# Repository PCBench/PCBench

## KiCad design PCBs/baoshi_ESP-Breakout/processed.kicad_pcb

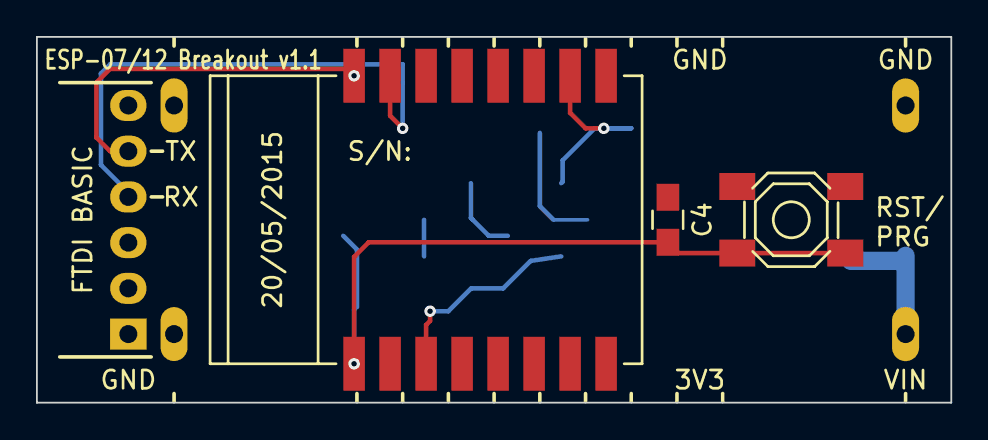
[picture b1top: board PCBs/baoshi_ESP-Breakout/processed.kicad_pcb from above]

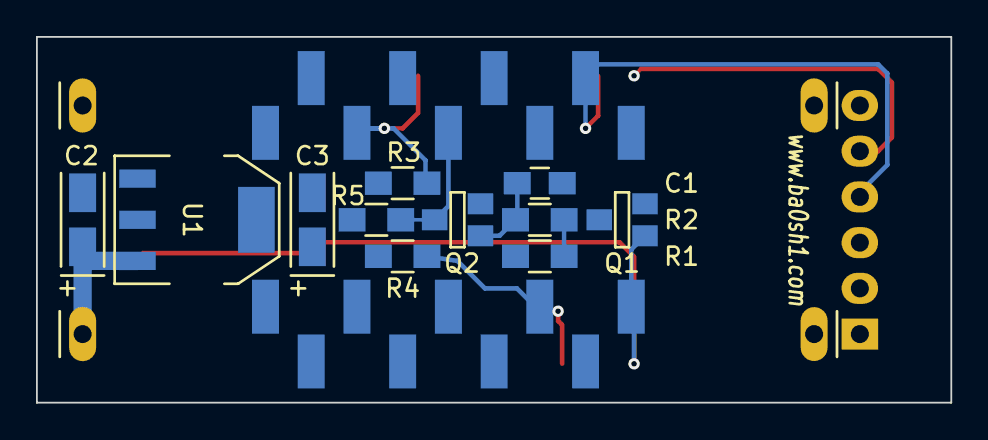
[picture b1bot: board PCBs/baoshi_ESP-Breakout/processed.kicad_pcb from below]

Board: 2 copper layers, 50.8 x 20.3 mm, 17 parts (13 on the bottom side), 9 nets.

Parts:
C1: 2u2; C_0805_HandSoldering
C2: 4u7; TantalC_SizeA_EIA-3216_Wave
C3: 22u; TantalC_SizeA_EIA-3216_Wave
C4: 0.1u; C_0805_HandSoldering
M1: ESP-07
P1: FTDI BASIC; Pin_Header_Angled_1x06
P2: CONN_01X11; SMD-PINHEADER-11A
P3: CONN_01X11; SMD-PINHEADER-11B
Q1, Q2: BSS138; SOT-23-GDS
R1: 470K; R_0805_HandSoldering
R2: 100K; R_0805_HandSoldering
R3, R5: 10K; R_0805_HandSoldering
R4: 47K; R_0805_HandSoldering
SW1: SW_PUSH; PUSH_4x4_SMD
U1: 1117-3.3; SOT-223

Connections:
+5V: P3.11, U1.3
/GPIO0: P2.6, Q2.D, R5.1
/RESET: C4.1, M1.1, P3.2, Q1.G, SW1.2
/RXI: M1.16, P1.5
/TXO: M1.15, P1.4
unnamed: C1.1, Q2.G, R2.1
unnamed: M1.3, R4.1
unnamed: M1.10, R3.2
unnamed: R1.2, R2.2

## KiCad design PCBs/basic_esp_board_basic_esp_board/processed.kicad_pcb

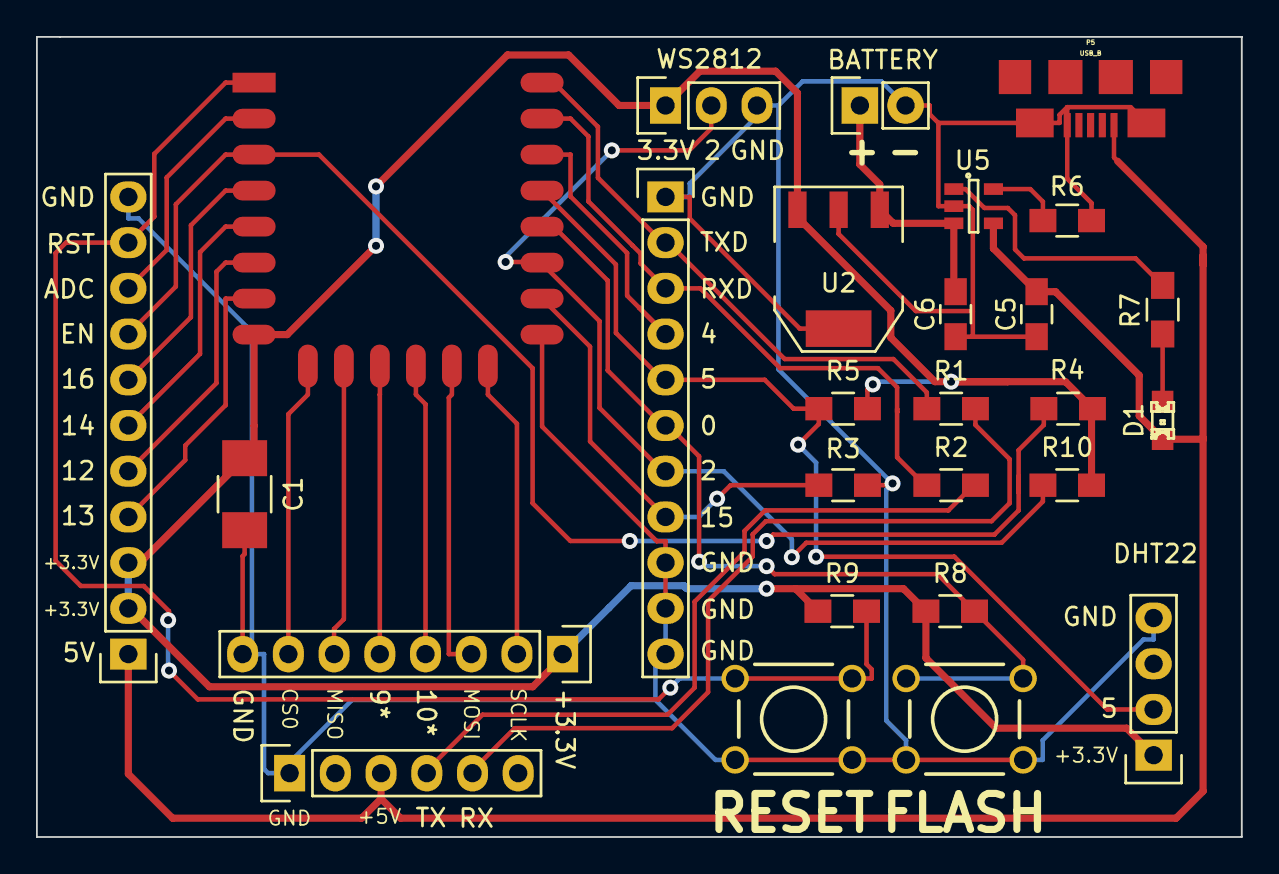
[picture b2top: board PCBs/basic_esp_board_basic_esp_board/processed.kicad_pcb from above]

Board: 2 copper layers, 66.9 x 44.4 mm, 27 parts (0 on the bottom side), 29 nets.

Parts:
BT1: BATTERY; Pin_Header_Straight_1x02
C1: 100uF 6.3V X5R; C_1210_HandSoldering
C5, C6: 4u7; C_0805_HandSoldering
D1: LED; LED-0805
P1: CONN_SERIAL_SF; Pin_Header_Straight_1x06
P2: HEADER_1; Socket_Strip_Straight_1x11
P3: HEADER_2; Socket_Strip_Straight_1x11
P4: HEADER_3; Socket_Strip_Straight_1x08
P5: USB_B; USBMICROB_HIROSE_ZX62_B_5PA
P6: WS2812; Pin_Header_Straight_1x03
R1, R2: 4.7k; R_0805_HandSoldering
R3, R4, R8, R9, R10: 10K; R_0805_HandSoldering
R5: 5.1K; R_0805_HandSoldering
R6: 2k; R_0805_HandSoldering
R7: 470; R_0805_HandSoldering
SW1: PROG; SW_PUSHBUTTON_PTH
SW2: RESET; SW_PUSHBUTTON_PTH
U1: ESP-12E
U2: TC1262-33VDB; SOT-223
U3: DHT22; Pin_Header_Straight_1x04
U5: MCP73831; SOT-23-5

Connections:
+3V3: C1.1, P3.2, P3.3, P4.1, P6.1, R4.1, R5.2, R8.1, R9.1, R10.2, U1.8, U2.3, U3.1
+5V: C5.1, D1.1, P1.3, P3.1, P5.1, U5.4
+BATT: BT1.1, C6.1, U2.1, U5.3
/ADC: P3.9, U1.2
/CS0: P4.7, U1.9
/EN: P3.8, R4.2, U1.3
/GPIO0: P2.6, R8.2, SW1.2, U1.18
/GPIO2: P2.7, P6.2, R10.1, U1.17
/GPIO4: P2.4, U1.20
/GPIO5: P2.5, R5.1, U1.19, U3.2
/GPIO9: P4.5, U1.11
/GPIO10: P4.4, U1.12
/GPIO12: P3.5, U1.6
/GPIO13: P3.4, U1.7
/GPIO14: P3.6, U1.5
/GPIO15: P2.8, R3.2, U1.16
/GPIO16: P3.7, U1.4
/MISO: P4.6, U1.10
/MOSI: P4.3, U1.13
/RESET: P3.10, R9.2, SW2.2, U1.1
/RXD: P2.3, R2.1, U1.21
/SCLK: P4.2, U1.14
/TXD: P2.2, R1.1, U1.22
GND: BT1.2, C1.2, C5.2, C6.2, P1.1, P2.1, P2.9, P2.10, P2.11, P3.11, P4.8, P5.4, P5.5, P6.3, R3.1, R6.2, SW1.1, SW2.1, U1.15, U2.2, U3.4, U5.2
unnamed: D1.2, R7.2
unnamed: P1.4, R2.2
unnamed: P1.5, R1.2
unnamed: R6.1, U5.5
unnamed: R7.1, U5.1

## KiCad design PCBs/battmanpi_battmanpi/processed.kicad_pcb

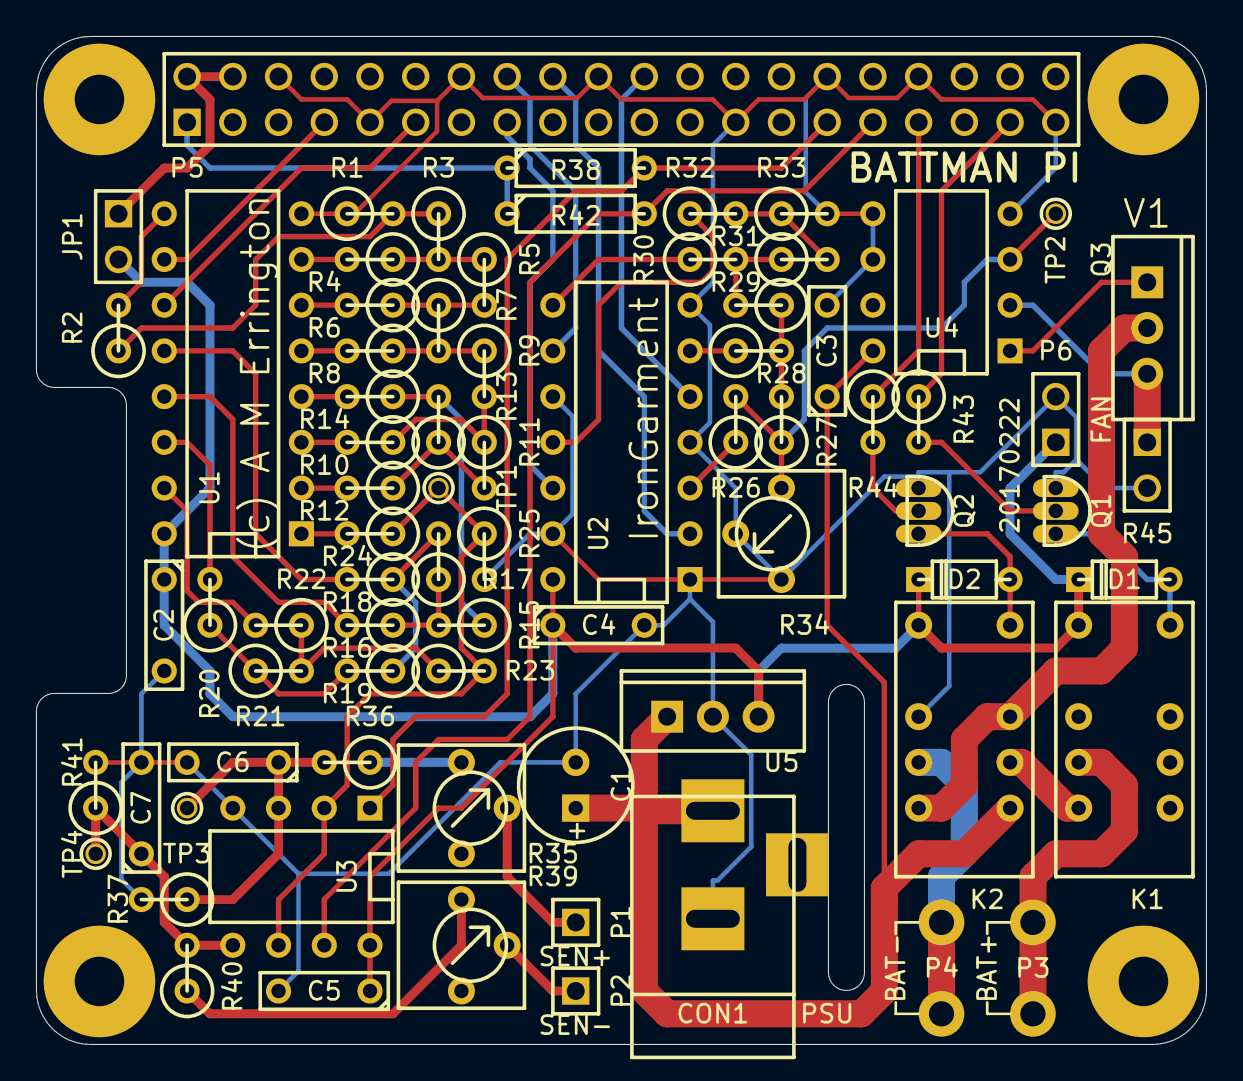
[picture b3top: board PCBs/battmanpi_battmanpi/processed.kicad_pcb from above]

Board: 2 copper layers, 65.0 x 56.0 mm, 80 parts (0 on the bottom side), 63 nets.

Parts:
C1: 10u; C1V7
C2, C3, C4, C5, C6, C7: 0.1u; C2
CON1: PSU; BARREL_JACK
D1, D2: 1N914; D3S
JP1: 5V link; PIN_ARRAY_2X1
K1, K2: TX2-5V; RELAY_FORMC
P1: SEN+; PIN_ARRAY_1
P2: SEN-; PIN_ARRAY_1
P3: BAT+; 635mmspade
P4: BAT-; 635mmspade
P5: Raspberry Pi; PIN_ARRAY_20X2
P6: FAN; PIN_ARRAY_2X1
Q1, Q2: 2N3904; TO92bulk
Q3: TIP120; TO220V
R1, R2, R4, R6, R8, R10, R12, R14, R16, R18, R20, R22, R24, R26, R28, R30, R32, R33, R37, R41: 20k; R1
R3, R5, R7, R9, R11, R13, R15, R17, R19, R21, R23, R27, R29, R31: 10k; R1
R25: 15k; R1
R34: 1k; 6mmSQ
R35, R39: 10k; 6mmSQ
R36, R40: 100k; R1
R38, R42: 4.7k; R3
R43, R44: 1k; R1
R45: 0.1 2W; PIN_ARRAY_2X1
TP1, TP2, TP3, TP4: TST; PINTST
U1: 74HCT4040; DIP-16__300
U2: 74HCT125; DIP-14__300
U3: LM393; DIP-8__300
U4: LM358; DIP-8__300
U5: 7805; TO220V
mounting_hole: VAL**; mounting_hole
mounting_hole_2, mounting_hole_3, mounting_hole_4: VAL**; mounting_hole

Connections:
+3.3V: P5.1, R38.1, R42.1
+5V: C2.1, C4.1, C5.1, D1.2, D2.2, JP1.2, K1.1, K2.1, P6.1, U1.16, U2.14, U3.8, U5.3
+24V: C1.1, C3.1, CON1.1, K2.8, U4.8, U5.1
/CNCT: P5.37, R43.1
/D0: P5.15, U2.12
/D1: P5.16, U2.9
/D2: P5.22, U2.5
/D3: P5.18, U2.2
/INCR: P5.7, U1.10
/MODE: P5.33, R44.1
/VDAC: R23.2, R24.1, R25.1, TP1.1, U3.2, U3.6
/VDAC<B+: P5.29, R38.2, U3.1
/VDAC<B-: P5.31, R42.2, U3.7
/ZERO: P5.11, U1.11
GND: C1.2, C2.2, C3.2, C4.2, C5.2, C6.2, C7.2, CON1.2, K2.3, P5.6, P5.9, P5.14, P5.20, P5.25, P5.30, P5.34, P5.39, P6.2, Q1.1, Q2.1, R1.1, R25.2, R33.2, R34.1, R34.2, R37.2, R41.2, R45.2, U1.8, U2.1, U2.4, U2.7, U2.10, U2.13, U3.4, U4.4, U4.5, U4.6, U5.2
unnamed: R39.1, R40.1
unnamed: R35.1, R36.1
unnamed: P1.1, R35.2
unnamed: P2.1, R39.2
unnamed: C6.1, R36.2, R37.1, TP3.1, U3.3
unnamed: C7.1, R40.2, R41.1, TP4.1, U3.5
unnamed: R12.2, U1.2
unnamed: R6.2, U1.6
unnamed: R8.2, U1.5
unnamed: R10.2, U1.3
unnamed: R14.2, U1.4
unnamed: R16.2, U1.13
unnamed: R18.2, U1.12
unnamed: R3.2, R4.1, R5.1
unnamed: R9.2, R10.1, R11.1
unnamed: R7.2, R8.1, R9.1
unnamed: R5.2, R6.1, R7.1
unnamed: R20.2, U1.14
unnamed: R1.2, R2.1, R3.1
unnamed: R2.2, U1.9
unnamed: R4.2, U1.7
unnamed: D1.1, K1.12, Q1.3
unnamed: K2.4, P4.1
unnamed: Q1.2, R43.2
unnamed: K1.4, P3.1
unnamed: K1.5, K2.9
unnamed: Q2.2, R44.2
unnamed: R22.2, U1.15
unnamed: R24.2, U1.1
unnamed: D2.1, K2.12, Q2.3
unnamed: K2.5, K2.10, Q3.2
unnamed: JP1.1, P5.2, P5.4
unnamed: R13.2, R14.1, R15.1
unnamed: R11.2, R12.1, R13.1
unnamed: R17.2, R18.1, R19.1
unnamed: R19.2, R20.1, R21.1
unnamed: R21.2, R22.1, R23.1
unnamed: R15.2, R16.1, R17.1
unnamed: R26.2, R27.1, R34.3, TP2.1, U4.3
unnamed: Q3.1, U4.1
unnamed: R31.2, R32.2, R33.1
unnamed: R26.1, U2.3
unnamed: R28.1, U2.6
unnamed: R27.2, R28.2, R29.1
unnamed: R30.1, U2.8
unnamed: R29.2, R30.2, R31.1
unnamed: R32.1, U2.11
unnamed: Q3.3, R45.1, U4.2

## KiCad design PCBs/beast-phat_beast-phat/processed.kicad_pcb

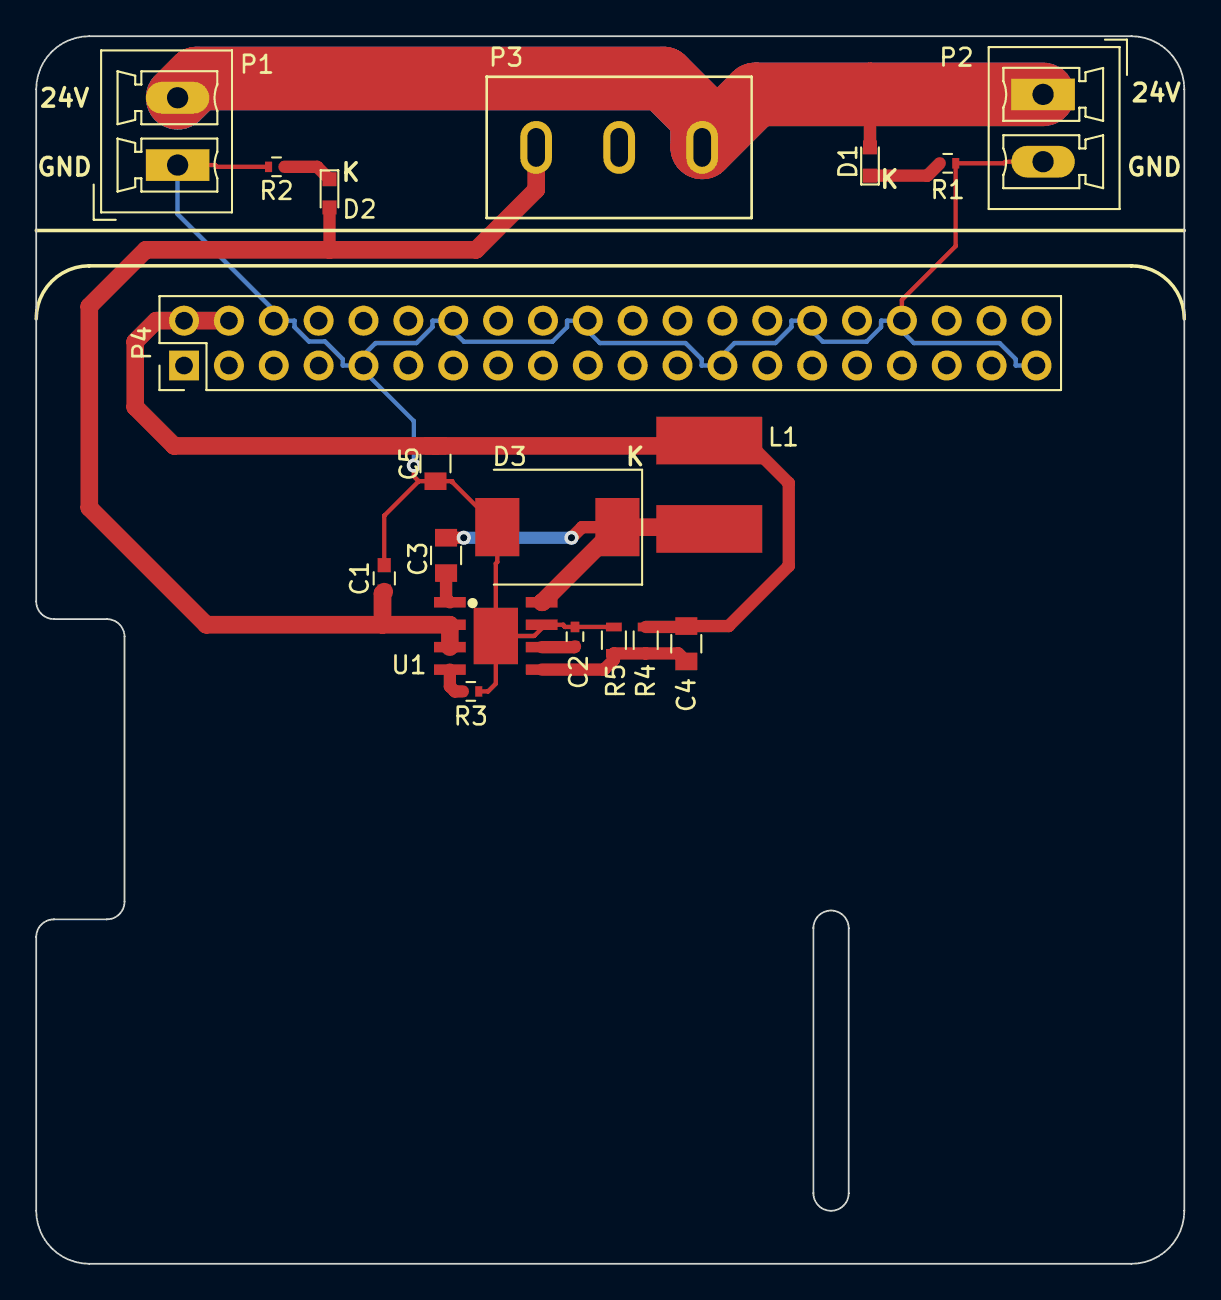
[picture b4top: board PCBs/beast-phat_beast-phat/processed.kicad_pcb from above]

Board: 2 copper layers, 65.0 x 69.5 mm, 19 parts (0 on the bottom side), 11 nets.

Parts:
C1: 4.7u; C_0603
C2: 8.2n; C_0402
C3: 100n; C_0805
C4: 120p; C_0805
C5: 47u; C_0805
D1, D2: LED; LED_0603
D3: SCHOTTKY; D_SMC_Standard
L1: 3.3u; SRN6045
P1: INPUT; PhoenixContact_MCV-G_02x3.81mm_Vertical
P2: OUTPUT; PhoenixContact_MCV-G_02x3.81mm_Vertical
P3: SWITCH; switch
P4: STACKING HEADER; Pin_Header_Straight_2x20_Pitch2.54mm
R1: 90K; R_0402
R2: 10K; R_0402
R3: 20K; R_0402
R4: 68K; R_0603
R5: 12K; R_0603
U1: LMR14030S; HSOP8

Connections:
/5V: C4.2, C5.2, L1.1, P4.2, P4.4, R4.1
GND: C1.1, C2.1, C5.1, D3.2, P1.1, P2.2, P4.6, P4.9, P4.14, P4.20, P4.25, P4.30, P4.34, P4.39, R1.2, R2.2, R3.2, R5.2, U1.7, U1.9
unnamed: C1.2, D2.2, P3.1, U1.2, U1.3
unnamed: C2.2, U1.6
unnamed: C3.1, D3.1, L1.2, U1.8
unnamed: C3.2, U1.1
unnamed: C4.1, R4.2, R5.1, U1.5
unnamed: D1.1, R1.1
unnamed: D1.2, P1.2, P2.1, P3.3
unnamed: D2.1, R2.1
unnamed: R3.1, U1.4

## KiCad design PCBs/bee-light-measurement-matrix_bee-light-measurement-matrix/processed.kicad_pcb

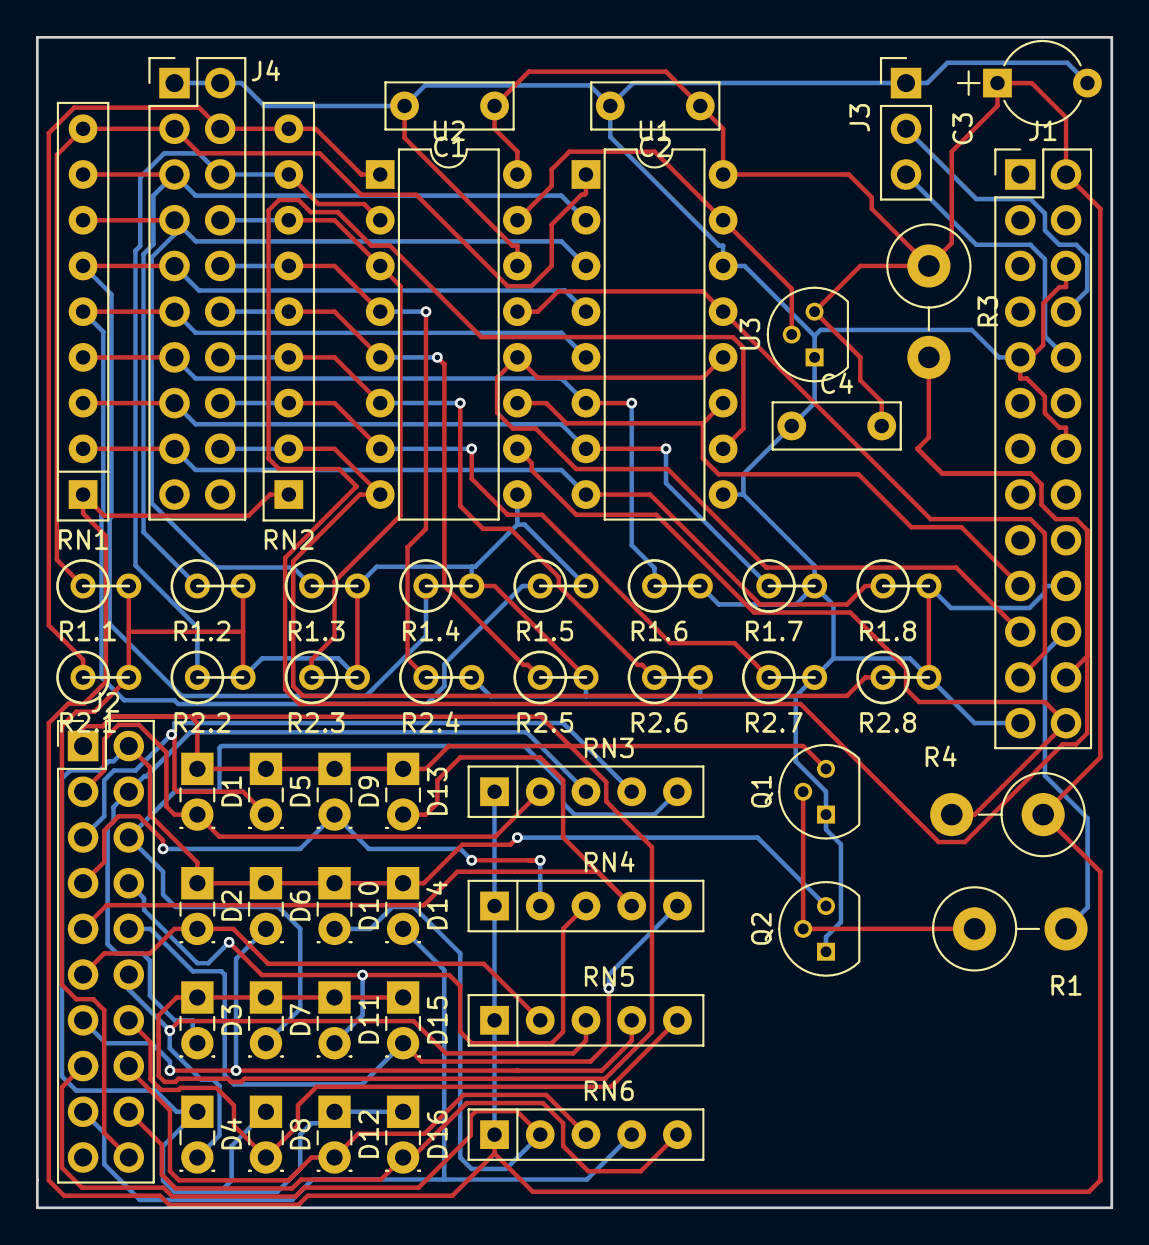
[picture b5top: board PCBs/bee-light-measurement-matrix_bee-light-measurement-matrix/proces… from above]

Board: 2 copper layers, 59.7 x 65.0 mm, 54 parts (0 on the bottom side), 46 nets.

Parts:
C1, C2, C4: 100n; C_Disc_D7.0mm_W2.5mm_P5.00mm
C3: 10µ; CP_Radial_Tantal_D4.5mm_P5.00mm
D1, D2, D3, D4, D5, D6, D7, D8, D9, D10, D11, D12, D13, D14, D15, D16: LED; LED_Rectangular_W3.9mm_H1.8mm_FlatTop
J1: CONN_02X13; Pin_Header_Straight_2x13_Pitch2.54mm
J2, J4: CONN_02X10; Pin_Header_Straight_2x10_Pitch2.54mm
J3: CONN_01X03; Pin_Header_Straight_1x03_Pitch2.54mm
Q1, Q2: 2N3904; TO-92_Molded_Narrow
R1: 4,7k; R_Axial_DIN0414_L11.9mm_D4.5mm_P5.08mm_Vertical
R1.1, R1.2, R1.3, R1.4, R1.5, R1.6, R1.7, R1.8, R2.1, R2.2, R2.3, R2.4, R2.5, R2.6, R2.7, R2.8: R_PHOTO; R1
R3, R4: 100k; R_Axial_DIN0414_L11.9mm_D4.5mm_P5.08mm_Vertical
RN1, RN2: R_Network08; R_Array_SIP9
RN3, RN4, RN5, RN6: R_Network04; R_Array_SIP5
U1, U2: MCP3208; DIP-16_W7.62mm
U3: MCP1541; TO-92_Molded_Narrow

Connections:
+5V: C1.1, C2.1, C3.1, C4.2, J1.2, R3.1, R4.1, RN1.1, RN2.1, RN3.1, RN4.1, RN5.1, RN6.1, U1.16, U2.16, U3.3
CE0: J1.24, R3.2, U1.10
CE1: J1.26, R4.2, U2.10
CLK: J1.23, U1.13, U2.13
GND: C1.2, C2.2, C3.2, C4.1, J1.6, J1.9, J1.14, J1.20, J1.25, J2.20, J3.1, J4.1, J4.2, Q1.1, Q2.1, R1.1.2, R1.2.2, R1.3.2, R1.4.2, R1.5.2, R1.6.2, R1.7.2, R1.8.2, R2.1.2, R2.2.2, R2.3.2, R2.4.2, R2.5.2, R2.6.2, R2.7.2, R2.8.2, U1.9, U1.14, U2.9, U2.14, U3.1
GPIO25: J1.22, R1.2
LED_D1: D1.1, D3.1, D5.1, D7.1, D9.1, D11.1, D13.1, D15.1, J2.1, Q1.3
LED_D1_1: D1.2, J2.3, RN3.2
LED_D1_2: D3.2, J2.4, RN3.3
LED_D1_3: D5.2, J2.5, RN3.4
LED_D1_4: D7.2, J2.6, RN3.5
LED_D1_5: D9.2, J2.7, RN4.2
LED_D1_6: D11.2, J2.8, RN4.3
LED_D1_7: D13.2, J2.9, RN4.4
LED_D1_8: D15.2, J2.10, RN4.5
LED_D2: D2.1, D4.1, D6.1, D8.1, D10.1, D12.1, D14.1, D16.1, J2.2, Q2.3
LED_D2_1: D2.2, J2.11, RN5.2
LED_D2_2: D4.2, J2.12, RN5.3
LED_D2_3: D6.2, J2.13, RN5.4
LED_D2_4: D8.2, J2.14, RN5.5
LED_D2_5: D10.2, J2.15, RN6.2
LED_D2_6: D12.2, J2.16, RN6.3
LED_D2_7: D14.2, J2.17, RN6.4
LED_D2_8: D16.2, J2.18, RN6.5
MISO: J1.21, U1.12, U2.12
MOSI: J1.19, U1.11, U2.11
unnamed: J4.3, R1.1.1, RN1.9, U1.1
unnamed: J4.4, R2.1.1, RN2.9, U2.1
unnamed: J4.5, R1.2.1, RN1.8, U1.2
unnamed: J4.6, R2.2.1, RN2.8, U2.2
unnamed: J4.7, R1.3.1, RN1.7, U1.3
unnamed: J4.8, R2.3.1, RN2.7, U2.3
unnamed: J4.9, R1.4.1, RN1.6, U1.4
unnamed: J4.10, R2.4.1, RN2.6, U2.4
unnamed: J4.11, R1.5.1, RN1.5, U1.5
unnamed: J4.12, R2.5.1, RN2.5, U2.5
unnamed: J4.13, R1.6.1, RN1.4, U1.6
unnamed: J4.14, R2.6.1, RN2.4, U2.6
unnamed: J4.15, R1.7.1, RN1.3, U1.7
unnamed: J4.16, R2.7.1, RN2.3, U2.7
unnamed: J4.17, R1.8.1, RN1.2, U1.8
unnamed: J4.18, R2.8.1, RN2.2, U2.8
unnamed: Q1.2, Q2.2, R1.1
RXD: J1.10, J3.3
TXD: J1.8, J3.2
Vref: U1.15, U2.15, U3.2

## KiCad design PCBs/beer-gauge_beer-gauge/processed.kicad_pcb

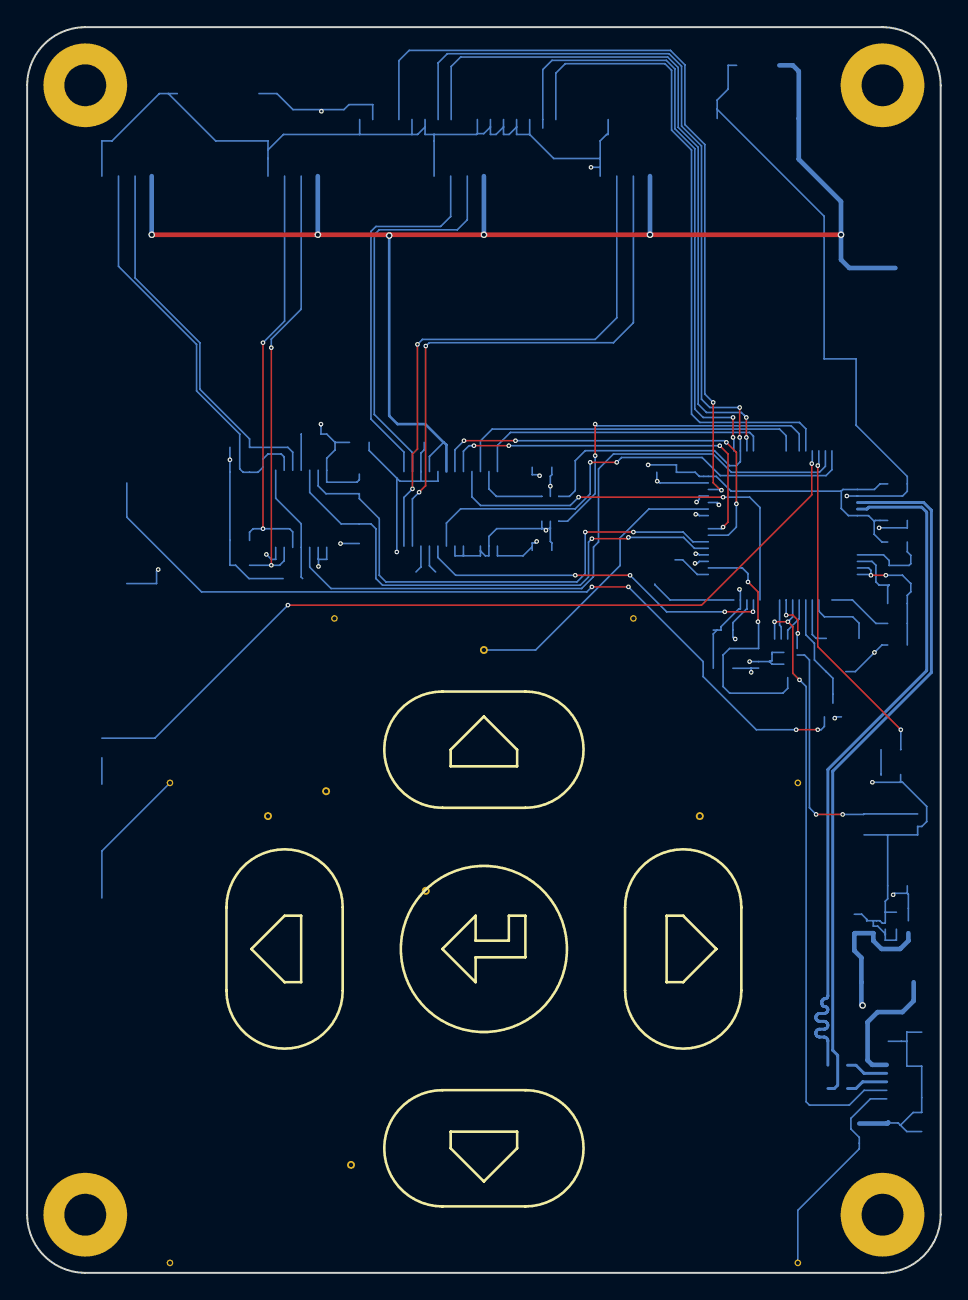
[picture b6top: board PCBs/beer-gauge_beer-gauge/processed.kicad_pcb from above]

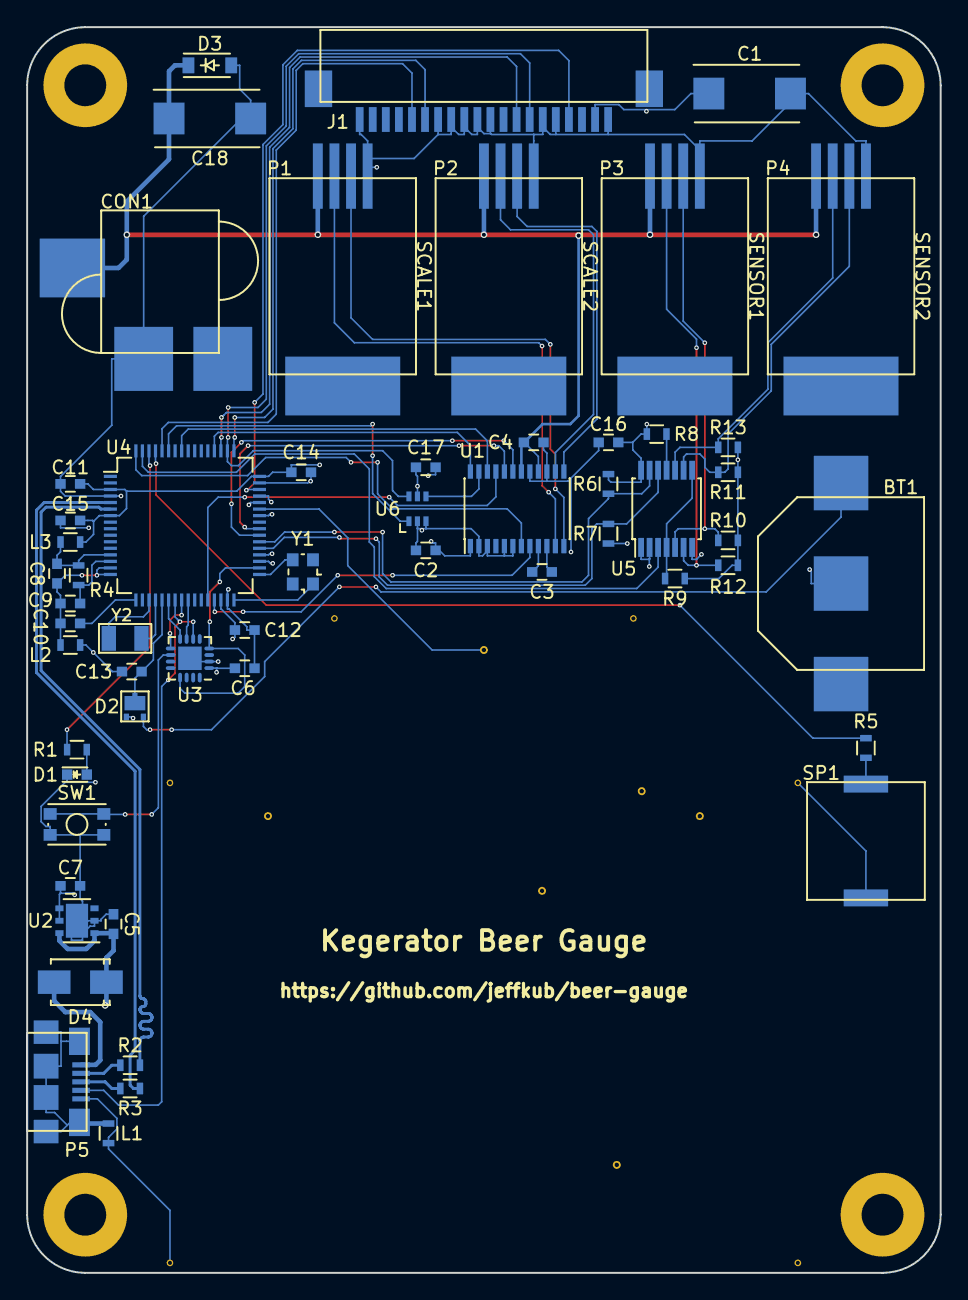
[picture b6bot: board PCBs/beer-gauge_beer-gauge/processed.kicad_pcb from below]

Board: 4 copper layers, 69.8 x 95.2 mm, 62 parts (56 on the bottom side), 64 nets.

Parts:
BT1: Battery; BK-885
C1: 220u; TantalC_SizeD_EIA-7343_Reflow
C2, C3, C4, C6, C9, C10, C11, C12, C13, C14, C16, C17: 0.1u; C_0603
C5, C7, C8, C15: 2.2u; C_0603
C18: 100u; TantalC_SizeD_EIA-7343_Reflow
CON1: BARREL_JACK; PJ-070AH-SMT
D1: LED; LED_0603
D2: PMEG4010CPA; SOT1061
D3: DDZ6V2B; SOD-123
D4: S1B; SMA_Standard
J1: OLED_MODULE; 0522712069
L1, L3: 600 Ohm/100 MHz; R_0603
L2: 600 Ohm/100 Mhz; R_0603
P1, P2, P3, P4: CONN_01X04; 0855135016
P5: USB_OTG; 10118192
R1, R4, R5: 470; R_0603
R2, R3: 33; R_0603
R6, R7, R8, R9, R10, R11, R12, R13: 4.7k; R_0603
SP1: PIEZO; PKMCS
SW1: SW_PUSH; SW_SPST_KMR2
U1: ADS1232; TSSOP-24_4.4x7.8mm_Pitch0.65mm
U2: LP38691; DFN-6-1EP_3x3mm_Pitch0.95mm
U3: MKL02Z32; QFN-16-1EP_3x3mm_Pitch0.5mm
U4: MK20DX256VLH7; LQFP-64_10x10mm_Pitch0.5mm
U5: TCA9543A; TSSOP-14_4.4x5mm_Pitch0.65mm
U6: SN74LVC1G58; SC-70-6
W1, W2, W3, W4, W5, W6: TEST_1P; PadVia
Y1: 16 MHz; Crystal_SMD_2520_4Pads
Y2: 32.768 kHz; ABS07

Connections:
+3V3: C1.1, C2.1, C6.1, C7.1, C11.1, C12.1, C14.1, C15.1, C16.1, C17.1, D2.2, J1.2, L3.1, R6.1, R7.1, R8.1, R9.1, R10.1, R11.1, R12.1, R13.1, U1.1, U2.4, U2.5, U3.1, U4.3, U4.7, U4.30, U4.48, U5.14, U6.5
+5V: C4.1, C5.1, C18.1, CON1.1, D3.1, D4.1, P1.1, P2.1, P3.1, P4.1, U1.16, U1.18, U2.1, U2.6
/Teensy/0: U1.19, U4.39
/Teensy/1: U1.20, U4.40
/Teensy/2: U1.22, U4.57
/Teensy/3: U1.21, U4.28
/Teensy/4: U1.8, U4.29
/Teensy/5: U1.7, U4.64
/Teensy/6: R5.2, U4.61
/Teensy/7: U4.59, U6.1
/Teensy/8: J1.16, U4.60
/Teensy/9: J1.4, U4.46
/Teensy/10: J1.15, U4.49
/Teensy/11: J1.8, U4.51
/Teensy/12: U1.24, U4.52
/Teensy/13: J1.7, U4.50, U6.6
/Teensy/15/A1: U4.43, W1.1
/Teensy/16/A2: U4.35, W2.1
/Teensy/17/A3: U4.36, W5.1
/Teensy/18/A4: R6.2, U4.38, U5.13
/Teensy/19/A5: R7.2, U4.37, U5.12
/Teensy/20/A6: R1.1, U4.62
/Teensy/21/A7: U4.63, U5.3
/Teensy/22/A8: U4.44, W3.1
/Teensy/23/A9: U4.45, W4.1
/Teensy/25: U4.42, W6.1
/Teensy/AREF: C9.1, R4.1, U4.14
/Teensy/ID: P5.4, U3.6, U4.23
/Teensy/RESET_B: U3.4, U3.13, U4.34
/Teensy/SWD_CLK: U3.8, U4.22
/Teensy/SWD_DIO: U3.7, U4.25
/Teensy/USB_D+: R3.1, U4.5
/Teensy/USB_D-: R2.1, U4.6
GND: BT1.2, C1.2, C2.2, C4.2, C5.2, C6.2, C7.2, C11.2, C12.2, C13.2, C14.2, C15.2, C16.2, C17.2, C18.2, CON1.2, D1.1, D3.2, J1.1, J1.5, J1.6, J1.10, J1.11, J1.12, J1.13, J1.14, J1.20, L1.2, L2.1, P1.4, P2.4, P3.4, P4.4, P5.5, SP1.2, SW1.1, U1.2, U1.3, U1.5, U1.6, U1.15, U1.17, U2.2, U2.7, U3.2, U3.17, U4.4, U4.31, U4.47, U5.1, U5.2, U5.7, U6.2, U6.3
unnamed: BT1.1, D2.1
unnamed: C3.1, U1.9
unnamed: C3.2, U1.10
unnamed: C8.1, L3.2, R4.2, U4.13
unnamed: C10.1, U4.17
unnamed: C8.2, C9.2, C10.2, L2.2, U4.15, U4.16
unnamed: C13.1, D2.3, U4.21
unnamed: D1.2, R1.2
unnamed: D4.2, P5.1
unnamed: L1.1, P5.6
unnamed: P1.2, U1.11
unnamed: P1.3, U1.12
unnamed: P2.2, U1.14
unnamed: P2.3, U1.13
unnamed: P3.2, R12.2, U5.6
unnamed: P3.3, R10.2, U5.5
unnamed: P4.2, R13.2, U5.10
unnamed: P4.3, R11.2, U5.9
unnamed: P5.2, R2.2
unnamed: P5.3, R3.2
unnamed: R5.1, SP1.1
unnamed: R8.2, U5.11
unnamed: R9.2, U5.4, U5.8
unnamed: SW1.2, U3.10
unnamed: U1.23, U6.4
unnamed: U3.9, U4.24
unnamed: U4.19, Y2.1
unnamed: U4.20, Y2.2
unnamed: U4.32, Y1.1
unnamed: U4.33, Y1.2

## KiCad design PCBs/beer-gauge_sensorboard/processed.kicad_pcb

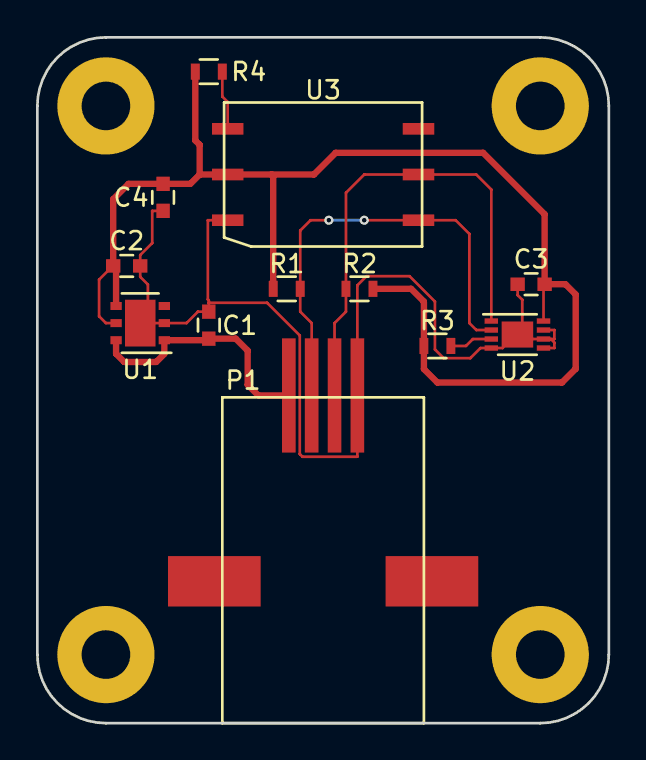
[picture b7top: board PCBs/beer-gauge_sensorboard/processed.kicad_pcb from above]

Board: 2 copper layers, 31.8 x 38.1 mm, 12 parts (0 on the bottom side), 7 nets.

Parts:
C1, C2: 2.2u; C_0603
C3, C4: 0.1u; C_0603
P1: CONN_01X04; 0855025005
R1, R2: DNP; R_0603
R3, R4: 4.7k; R_0603
U1: LP38691; DFN-6-1EP_3x3mm_Pitch0.95mm
U2: MCP9808; DFN-8-1EP_3x2mm_Pitch0.5mm
U3: ABPMANN030PG2A3

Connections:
+3V3: C2.1, C3.1, C4.1, R1.1, R2.1, R3.1, R4.1, U1.4, U1.5, U2.8, U3.2
+5V: C1.1, P1.1, U1.1, U1.6
/I2C_SCL: P1.2, R1.2, U2.2, U3.6
/I2C_SDA: P1.3, R2.2, U2.1, U3.5
GND: C1.2, C2.2, C3.2, C4.2, P1.4, U1.2, U1.7, U2.4, U2.5, U2.6, U2.7, U2.9, U3.1
unnamed: R3.2, U2.3
unnamed: R4.2, U3.3
